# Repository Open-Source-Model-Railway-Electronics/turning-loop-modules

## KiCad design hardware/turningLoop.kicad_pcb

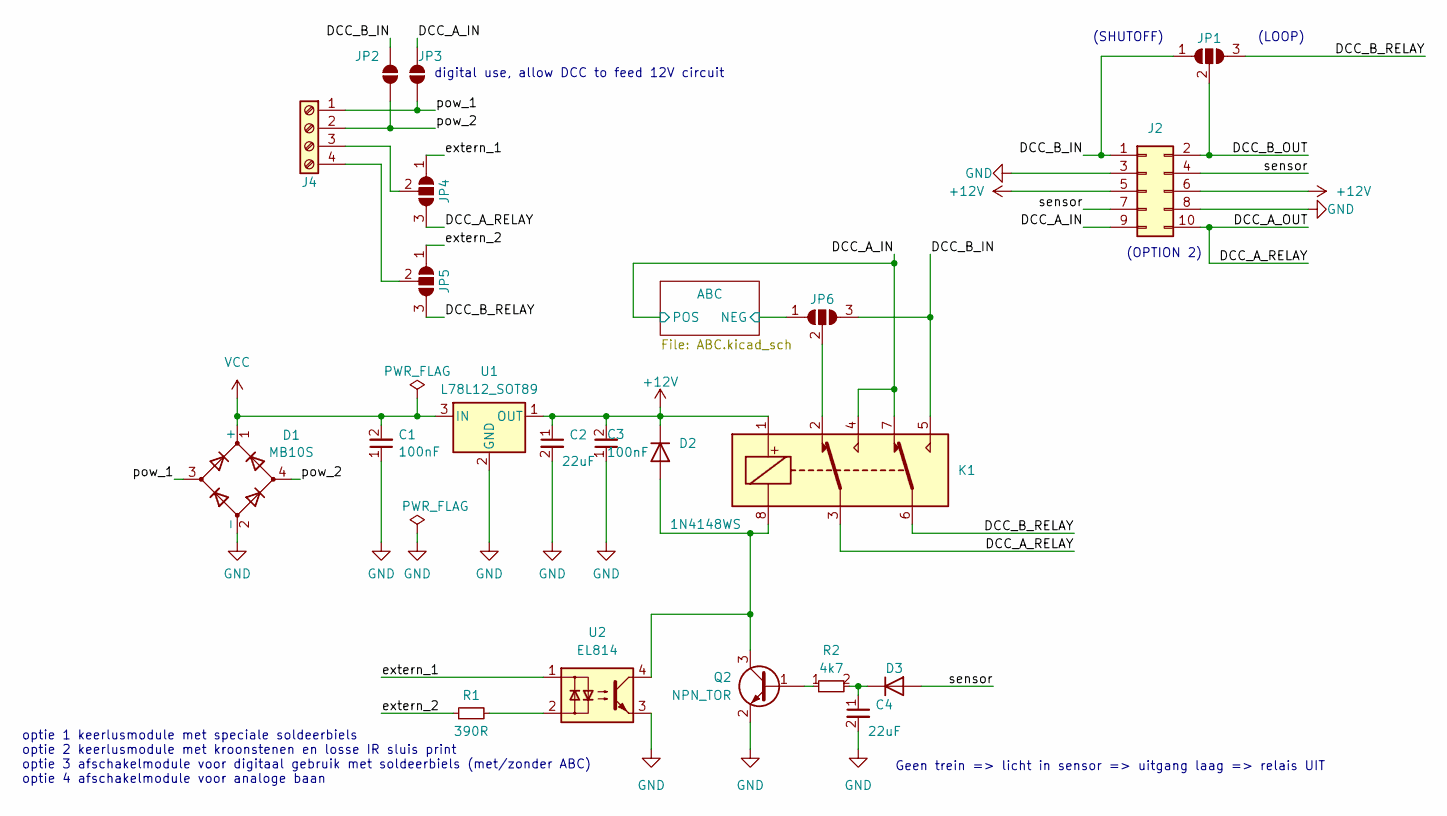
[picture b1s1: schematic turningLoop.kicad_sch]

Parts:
C1, C3: 100nF; C_0603_1608Metric; JLCPCB Part# C14663
C2, C4: 22uF; C_1206_3216Metric; JLCPCB Part# C12891
D1: MB10S; MB10s; JLCPCB Part# C2488
D2, D3: 1N4148WS; D_SOD-323; JLCPCB Part# C2128
J2: Conn_02x05_Odd_Even; PinHeader_2x05_P2.54mm_Horizontal
J4: Screw_Terminal_01x04; PhoenixContact_MC_1,5_4-G-3.5_1x04_P3.50mm_Horizontal; JLCPCB Part# C880574
JP1, JP4, JP5, JP6: SolderJumper_3_Open; SolderJumper-3_P1.3mm_Open_RoundedPad1.0x1.5mm
JP2, JP3: SolderJumper_2_Open; SolderJumper-2_P1.3mm_Open_RoundedPad1.0x1.5mm
K1: G6K-2F-Y-TR DC5; Relay_DPDT_Omron_G6K-2F-Y; JLCPCB Part# C397194
Q2: NPN_TOR; SOT-23; JLCPCB Part# C2145
R1: 390R; R_0603_1608Metric; JLCPCB Part# C23151
R2: 4k7; R_0603_smalltext; JLCPCB Part# C23162
U1: L78L12_SOT89; SOT-89-3; JLCPCB Part# C75501
U2: EL814; SMDIP-4_W9.53mm; JLCPCB Part# C500388

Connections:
+12V: C2.1, C3.2, D2.1 (K), J2.5, J2.6, K1.1, U1.1 (OUT)
/ABC/NEG: JP6.1 (A); also elsewhere on the board
/DCC_A_IN: J2.9, JP3.2 (B), K1.4, K1.7; also elsewhere on the board
/DCC_A_OUT: J2.10, JP4.3 (B), K1.3
/DCC_B_IN: J2.1, JP1.1 (A), JP2.2 (B), JP6.3 (B), K1.5
/DCC_B_OUT: J2.2, JP1.2 (C)
/DCC_B_RELAY: JP1.3 (B), JP5.3 (B), K1.6
/extern_1: JP4.1 (A), U2.1
/extern_2: JP5.1 (A), R1.1
/pow_1: D1.3, J4.1, JP3.1 (A)
/pow_2: D1.4, J4.2, JP2.1 (A)
/sensor: D3.2 (A), J2.4, J2.7
GND: C1.1, C2.2, C3.1, C4.2, D1.2 (-), J2.3, J2.8, Q2.2 (E), U1.2 (GND), U2.3
unnamed: D2.2 (A), K1.8, Q2.3 (C), U2.4
unnamed: C4.1, D3.1 (K), R2.2
unnamed: J4.3, JP4.2 (C)
unnamed: J4.4, JP5.2 (C)
unnamed: JP6.2 (C), K1.2
unnamed: Q2.1 (B), R2.1
unnamed: R1.2, U2.2
VCC: C1.2, D1.1 (+), U1.3 (IN)

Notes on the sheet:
digital use, allow DCC to feed 12V circuit
(OPTION 2)
optie 1 keerlusmodule met speciale soldeerbiels optie 2 keerlusmodule met kroonstenen en losse IR sluis print optie 3 afschakelmodule voor digitaal gebruik met soldeerbiels (met/zonder ABC) optie 4 afschakelmodule voor analoge baan
(SHUTOFF)
(LOOP)
Geen trein => licht in sensor => uitgang laag => relais UIT

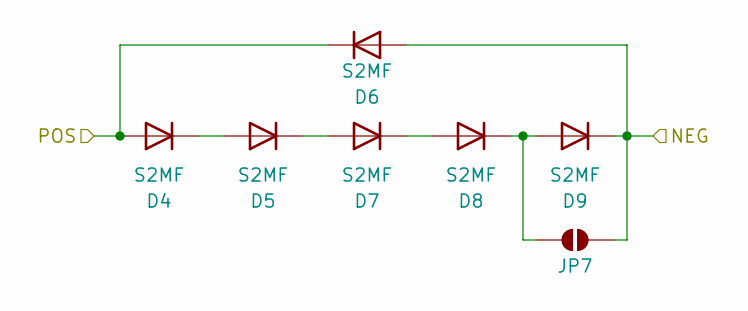
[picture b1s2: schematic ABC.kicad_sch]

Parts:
D4, D5, D6, D7, D8, D9: S2MF; S2MF_DIODE; JLCPCB Part# C5125722
JP7: SolderJumper_2_Open; SolderJumper-2_P1.3mm_Open_RoundedPad1.0x1.5mm

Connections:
/ABC/NEG: D6.2 (A), D9.1 (K), JP7.1 (A); also elsewhere on the board
/DCC_A_IN: D4.2 (A), D6.1 (K); also elsewhere on the board
unnamed: D4.1 (K), D5.2 (A)
unnamed: D5.1 (K), D7.2 (A)
unnamed: D7.1 (K), D8.2 (A)
unnamed: D8.1 (K), D9.2 (A), JP7.2 (B)

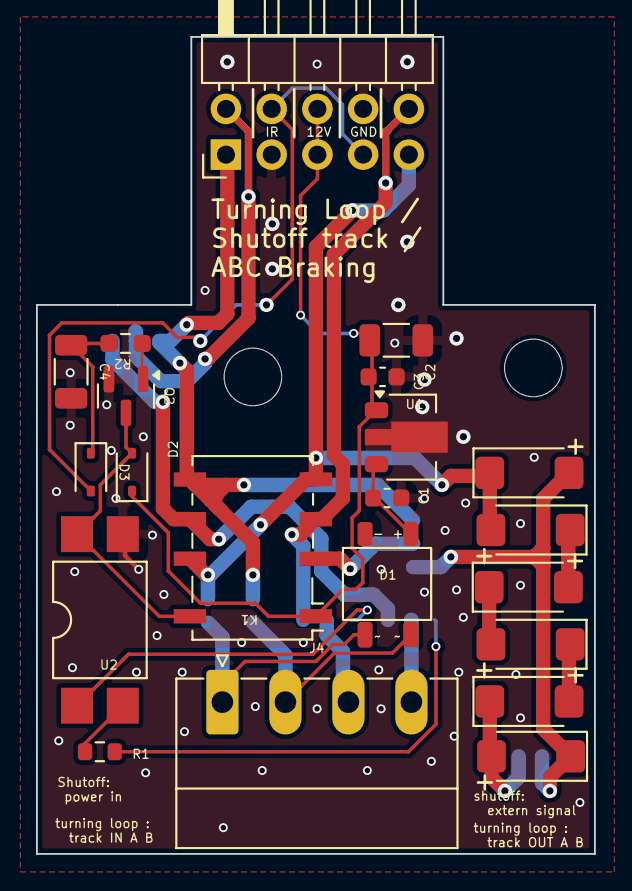
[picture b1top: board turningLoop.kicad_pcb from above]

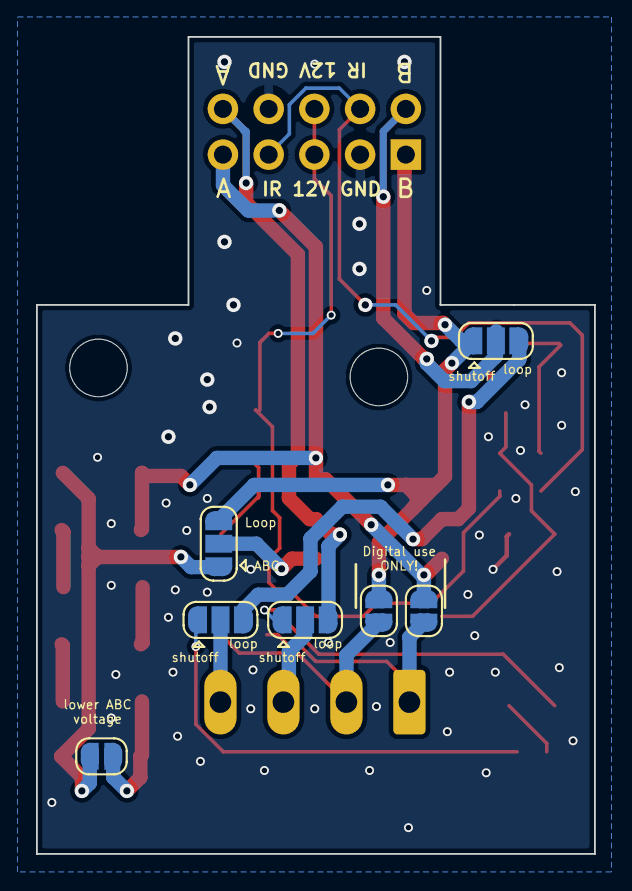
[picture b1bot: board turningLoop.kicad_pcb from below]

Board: 2 copper layers, 31.0 x 45.4 mm, 28 parts (7 on the bottom side), 25 nets.

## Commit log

2025-06-14 made production files
2025-06-17 added or renamed PNG preview
2025-06-19 Toegevoegd: handleiding (manual.odt)
2025-06-19 Hersteld: handleiding toegevoegd in docs/
